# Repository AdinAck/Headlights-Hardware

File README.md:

# Headlights-Hardware

This repo contains the PCB design files for the headlights board.

# Design Considerations

- high voltage compliance required great care for component selection and stray interactions
- the very high switching frequency of the half-bridge made the position and proximity of the components very important
- device failures must result in a safe state

---
[Firmware](https://github.com/AdinAck/Headlights-Firmware) | [App](https://github.com/AdinAck/Headlights-App)

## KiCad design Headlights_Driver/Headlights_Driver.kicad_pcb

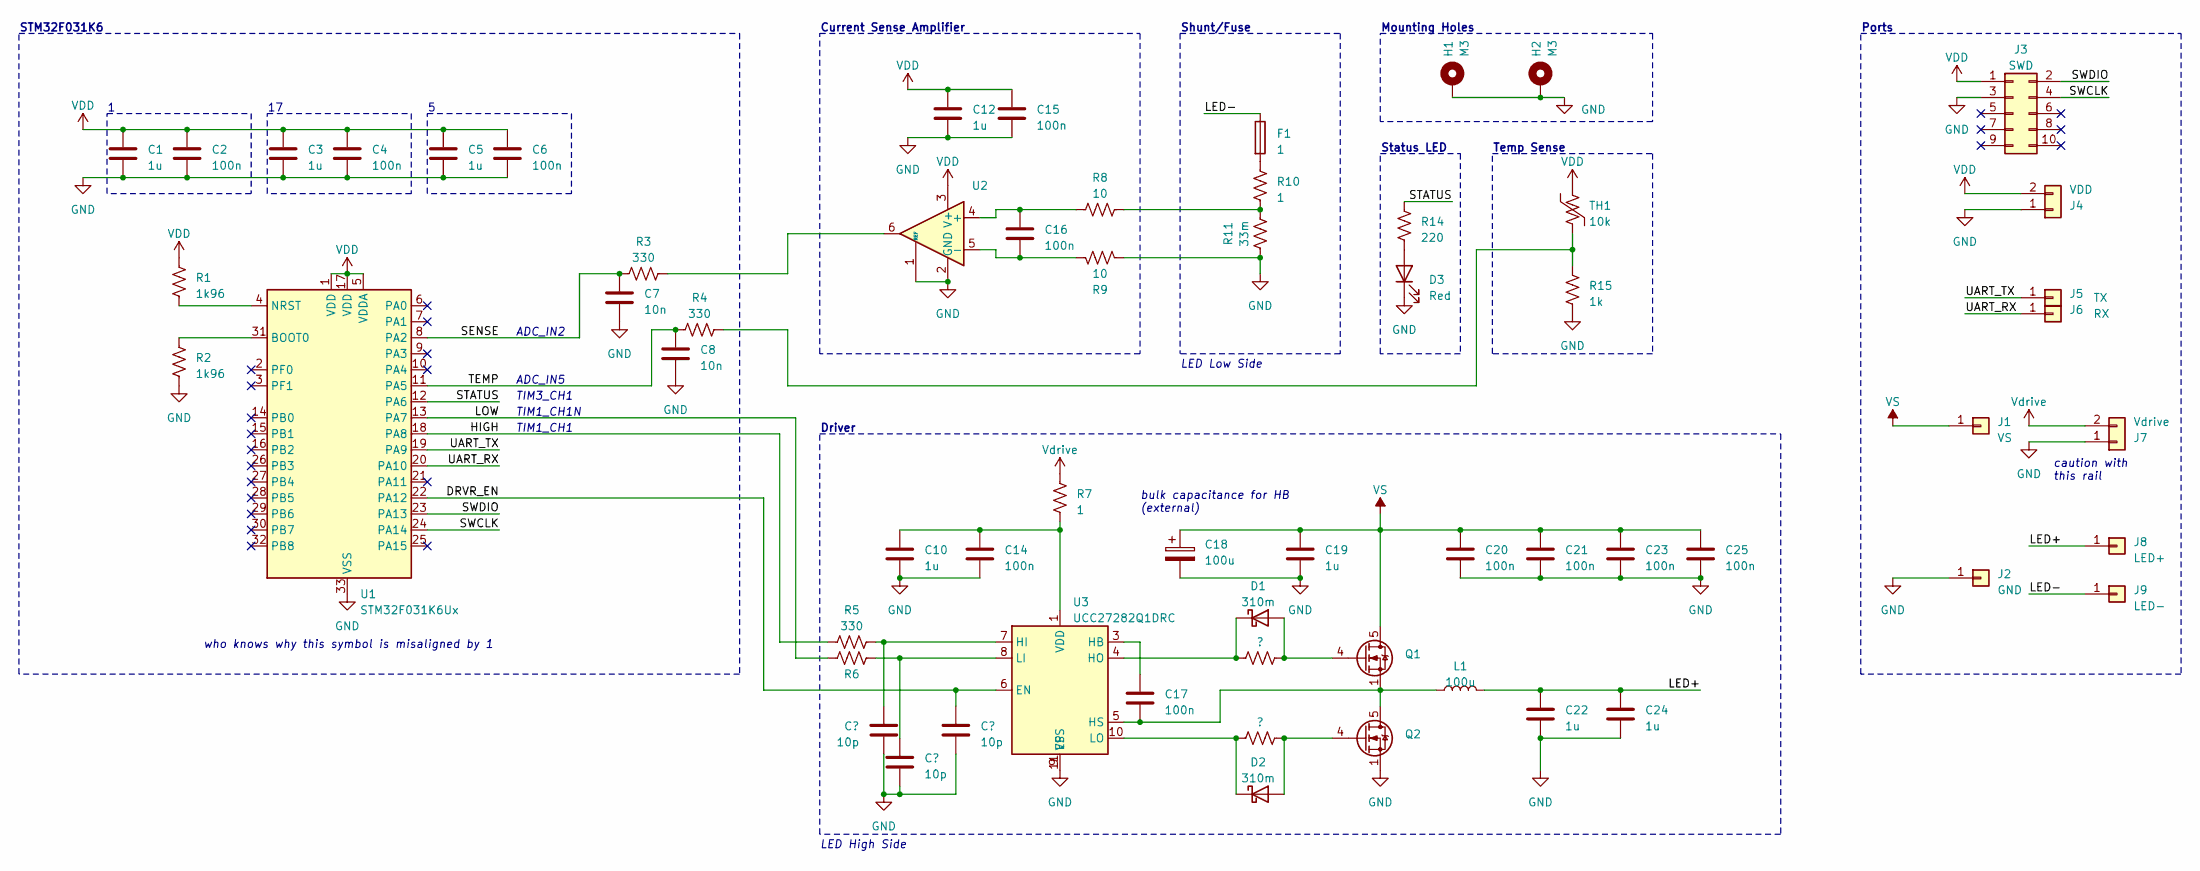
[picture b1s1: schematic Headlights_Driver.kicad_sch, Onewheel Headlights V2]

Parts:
C1, C3, C5, C10, C12: 1u; C_0402_1005Metric
C2, C4, C6, C14, C15, C16: 100n; C_0402_1005Metric
C7, C8: 10n; C_0402_1005Metric
C9, C11, C13: 10p; C_0402_1005Metric
C17, C20, C21, C23, C25: 100n; C_1206_3216Metric
C18: 100u
C19, C22, C24: 1u; C_2220_5650Metric
D1, D2: 310m; D_SOD-523
D3: Red; LED_0603_1608Metric
F1: 1; Fuse_0402_1005Metric
H1, H2: M3; MountingHole_3.2mm_M3_Pad_Via
J1: VS; SolderWirePad_1x01_SMD_4x6mm
J2: GND; SolderWirePad_1x01_SMD_4x6mm
J3: SWD; M50-3600542
J4: VDD; SolderWire-0.25sqmm_1x02_P4.2mm_D0.65mm_OD1.7mm
J5: TX; SolderWirePad_1x01_SMD_1x2mm
J6: RX; SolderWirePad_1x01_SMD_1x2mm
J7: Vdrive; SolderWire-0.25sqmm_1x02_P4.2mm_D0.65mm_OD1.7mm
J8: LED+; SolderWirePad_1x01_SMD_4x6mm
J9: LED-; SolderWirePad_1x01_SMD_4x6mm
L1: 100u; L_Bourns-SRN8040_8x8.15mm
Q1, Q2: BSC190N12NS3G; TDSON-8-1
R1, R2: 1k96; R_0402_1005Metric
R3, R4, R5, R6: 330; R_0402_1005Metric
R7: 1; R_0402_1005Metric
R8, R9: 10; R_0402_1005Metric
R10: 1; R_1206_3216Metric
R11: 33m; R_1206_3216Metric
R12, R13: ?; R_0402_1005Metric
R14: 220; R_0402_1005Metric
R15: 1k; R_0402_1005Metric
TH1: 10k; R_0402_1005Metric
U1: STM32F031K6Ux; QFN-32-1EP_5x5mm_P0.5mm_EP3.45x3.45mm
U2: INA199A2DCKR; SOT-363_SC-70-6
U3: UCC27282Q1DRC; VSON-10-1EP_3x3mm_P0.5mm_EP1.65x2.4mm_ThermalVias

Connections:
/DRVR_EN: C13.1, U1.22 (PA12), U3.6 (EN)
/HIGH: R5.1, U1.18 (PA8)
/LED+: C22.1, C24.1, J8.1, L1.2
/LED-: F1.1, J9.1
/LOW: R6.2, U1.13 (PA7)
/SENSE: C7.1, R3.1, U1.8 (PA2)
/STATUS: R14.1, U1.12 (PA6)
/SWCLK: J3.4, U1.24 (PA14)
/SWDIO: J3.2, U1.23 (PA13)
/TEMP: C8.1, R4.1, U1.11 (PA5)
/UART_RX: J6.1, U1.20 (PA10)
/UART_TX: J5.1, U1.19 (PA9)
GND: C1.2, C2.2, C3.2, C4.2, C5.2, C6.2, C7.2, C8.2, C9.2, C10.2, C11.2, C12.2, C13.2, C14.2, C15.2, C18.2, C19.2, C20.2, C21.2, C22.2, C23.2, C24.2, C25.2, D3.1 (K), H1.1, H2.1, J2.1, J3.3, J4.1, J7.1, Q2.1 (S), Q2.2 (S), Q2.3 (S), R2.2, R9.2, R11.2, R15.2, U1.33 (VSS), U2.1 (REF), U2.2 (GND), U3.9 (VSS), U3.11 (EP)
unnamed: D1.2 (A), Q1.4 (G), R12.2
unnamed: D1.1 (K), R12.1, U3.4 (HO)
unnamed: D2.2 (A), Q2.4 (G), R13.2
unnamed: D2.1 (K), R13.1, U3.10 (LO)
unnamed: D3.2 (A), R14.2
unnamed: F1.2, R10.1
unnamed: C17.2, L1.1, Q1.1 (S), Q1.2 (S), Q1.3 (S), Q2.5 (D), U3.5 (HS)
unnamed: R3.2, U2.6
unnamed: R8.2, R10.2, R11.1
unnamed: R4.2, R15.1, TH1.2
unnamed: R2.1, U1.31 (BOOT0)
unnamed: R1.2, U1.4 (NRST)
unnamed: C16.1, R8.1, U2.4 (+)
unnamed: C16.2, R9.1, U2.5 (-)
unnamed: C17.1, U3.3 (HB)
unnamed: C9.1, R5.2, U3.7 (HI)
unnamed: C11.1, R6.1, U3.8 (LI)
unnamed: C10.1, C14.1, R7.1, U3.1 (VDD)
VDD: C1.1, C2.1, C3.1, C4.1, C5.1, C6.1, C12.1, C15.1, J3.1, J4.2, R1.1, TH1.1, U1.1 (VDD), U1.5 (VDDA), U1.17 (VDD), U2.3 (V+)
VS: C18.1, C19.1, C20.1, C21.1, C23.1, C25.1, J1.1, Q1.5 (D)
Vdrive: J7.2, R7.2

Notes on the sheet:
Current Sense Amplifier
ADC_IN5
Ports
Shunt/Fuse
STM32F031K6
caution with this rail
LED Low Side
TIM3_CH1
Driver
bulk capacitance for HB (external)
Status LED
TIM1_CH1N
LED High Side
ADC_IN2
TIM1_CH1
Mounting Holes
who knows why this symbol is misaligned by 1
Temp Sense

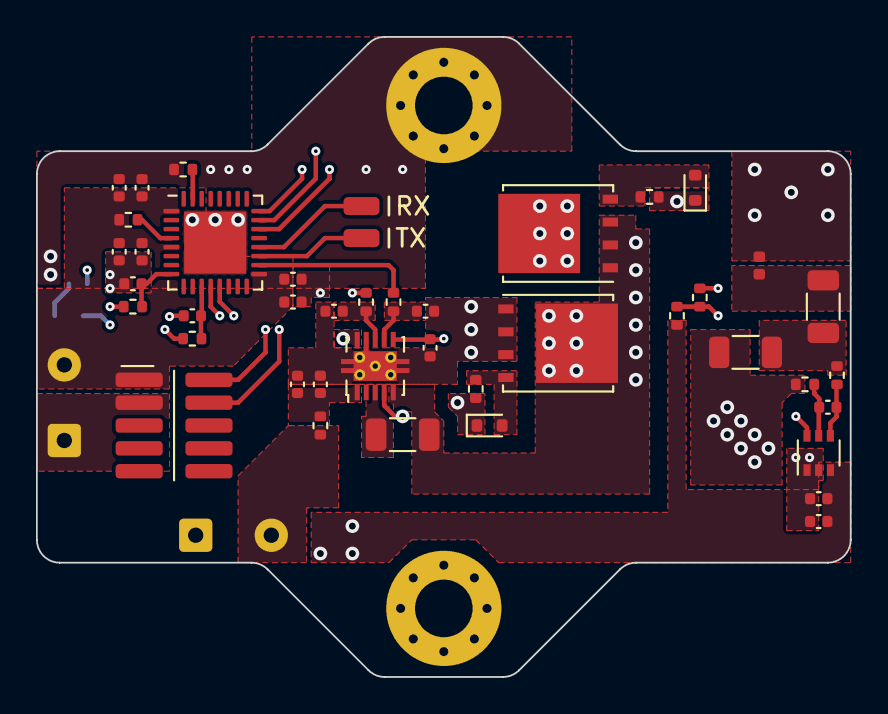
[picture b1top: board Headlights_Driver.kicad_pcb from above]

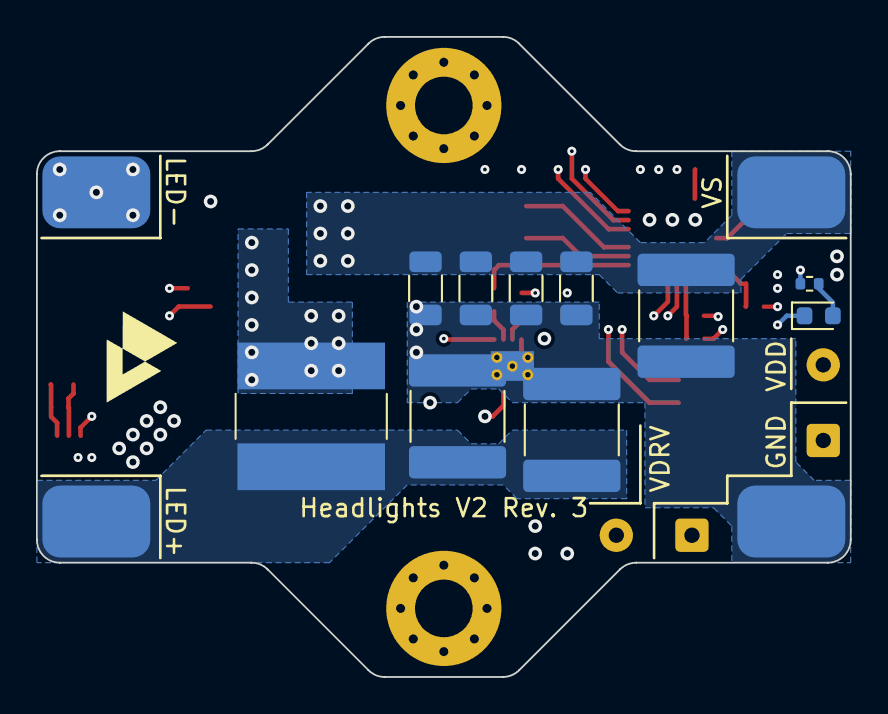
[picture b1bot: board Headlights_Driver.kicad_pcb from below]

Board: 4 copper layers, 45.2 x 35.6 mm, 61 parts (16 on the bottom side), 34 nets.

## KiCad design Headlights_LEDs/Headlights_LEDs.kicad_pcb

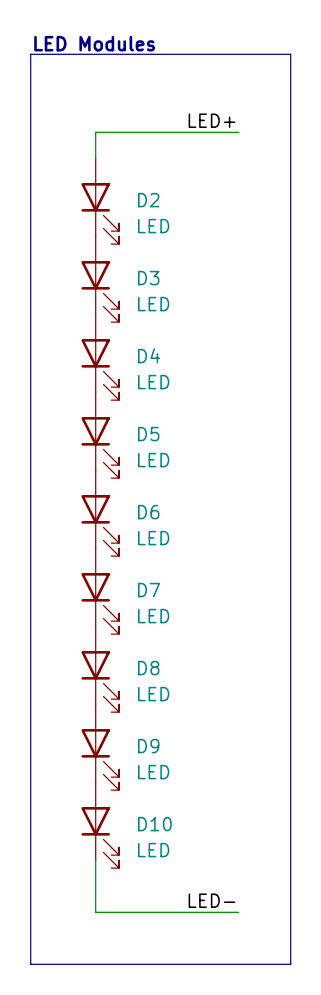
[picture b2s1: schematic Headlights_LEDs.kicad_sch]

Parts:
D2, D3, D4, D5, D6, D7, D8, D9, D10: LED; LED_5050; Part L150-40905006000S0

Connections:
/LED+: D2.2 (A)
/LED-: D10.1 (K)
unnamed: D2.1 (K), D3.2 (A)
unnamed: D3.1 (K), D4.2 (A)
unnamed: D4.1 (K), D5.2 (A)
unnamed: D5.1 (K), D6.2 (A)
unnamed: D6.1 (K), D7.2 (A)
unnamed: D7.1 (K), D8.2 (A)
unnamed: D8.1 (K), D9.2 (A)
unnamed: D9.1 (K), D10.2 (A)

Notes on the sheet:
LED Modules

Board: 2 copper layers, 9 parts (0 on the bottom side), 8 nets, no tracks yet.
